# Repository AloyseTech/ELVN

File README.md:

# ELVN

ELVN is ARM Cortex M0+ development board based on the SAMD11 microcontroller. This repository contains hardware and firmware related to this board, including development tool (host software etc).

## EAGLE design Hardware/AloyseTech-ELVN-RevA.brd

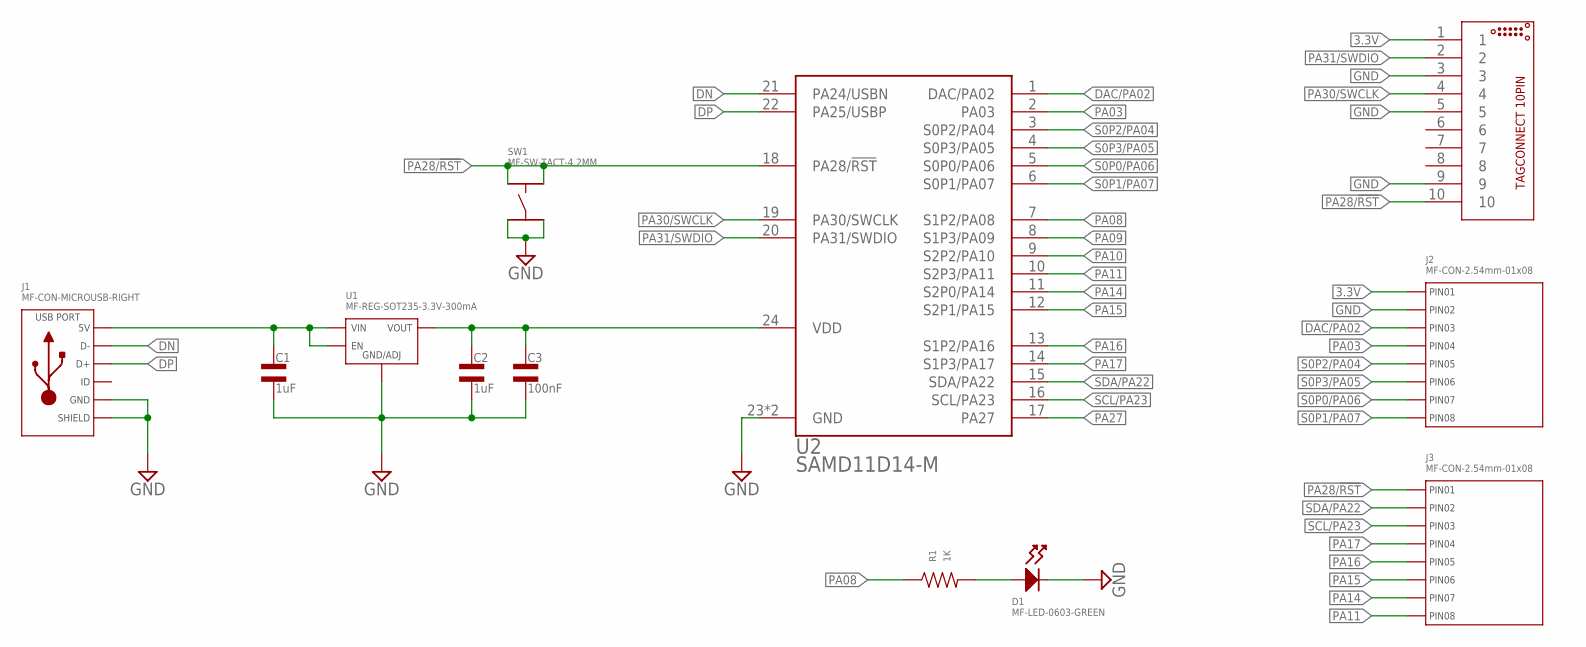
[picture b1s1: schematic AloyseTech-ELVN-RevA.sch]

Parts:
C1, C2: 1uF; 0805
C3: 100nF; 0402
D1: MF-LED-0603-GREEN; LED0603
J1: MF-CON-MICROUSB-RIGHT; MICROUSB-RIGHT
J2, J3: MF-CON-2.54mm-01x08; PTH_2.54MM_01X08
J4: TC2050-COMBO-NC; TC2050-10PIN1.27MM-COMBO-NC
R1: 1K; R0402
SW1: MF-SW-TACT-4.2MM; TACT4.2MM
U1: MF-REG-SOT235-3.3V-300mA; SOT-23-5
U2: SAMD11D14-M; QFN50P400X400X90-25T275

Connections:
3.3V: C2.1, C3.1, J2.P$1 (PIN1), J4.1, U1.P$5 (VOUT), U2.24 (VDD)
DAC/PA02: J2.P$3 (PIN3), U2.1 (DAC/PA02)
DN: J1.2 (D-), U2.21 (PA24/USBN)
DP: J1.3 (D+), U2.22 (PA25/USBP)
GND: C1.2, C2.2, C3.2, D1.CATHODE, J1.5 (GND), J1.S1 (SLD), J1.S2 (SLD), J1.S3 (SLD), J1.S4 (SLD), J1.S5 (SLD), J1.S6 (SLD), J2.P$2 (PIN2), J4.3, J4.5, J4.9, SW1.P$3, SW1.P$4, U1.P$2 (GND/ADJ), U2.23 (GND), U2.25 (GND)
unnamed: D1.ANODE, R1.P$2
PA03: J2.P$4 (PIN4), U2.2 (PA03)
PA08: R1.P$1, U2.7 (S1P2/PA08)
PA09: U2.8 (S1P3/PA09)
PA10: U2.9 (S2P2/PA10)
PA11: J3.P$8 (PIN8), U2.10 (S2P3/PA11)
PA14: J3.P$7 (PIN7), U2.11 (S2P0/PA14)
PA15: J3.P$6 (PIN6), U2.12 (S2P1/PA15)
PA16: J3.P$5 (PIN5), U2.13 (S1P2/PA16)
PA17: J3.P$4 (PIN4), U2.14 (S1P3/PA17)
PA27: U2.17 (PA27)
PA28/!RST!: J3.P$1 (PIN1), J4.10, SW1.P$1, SW1.P$2, U2.18 (PA28/!RST!)
PA30/SWCLK: J4.4, U2.19 (PA30/SWCLK)
PA31/SWDIO: J4.2, U2.20 (PA31/SWDIO)
S0P0/PA06: J2.P$7 (PIN7), U2.5 (S0P0/PA06)
S0P1/PA07: J2.P$8 (PIN8), U2.6 (S0P1/PA07)
S0P2/PA04: J2.P$5 (PIN5), U2.3 (S0P2/PA04)
S0P3/PA05: J2.P$6 (PIN6), U2.4 (S0P3/PA05)
SCL/PA23: J3.P$3 (PIN3), U2.16 (SCL/PA23)
SDA/PA22: J3.P$2 (PIN2), U2.15 (SDA/PA22)
VBUS: C1.1, J1.1 (5V), U1.P$1 (VIN), U1.P$3 (EN)

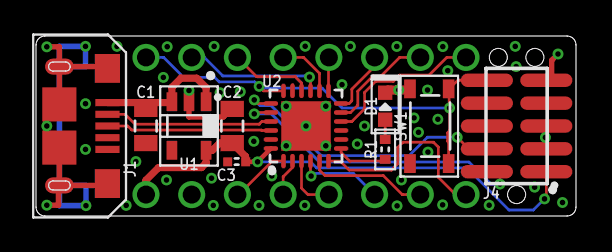
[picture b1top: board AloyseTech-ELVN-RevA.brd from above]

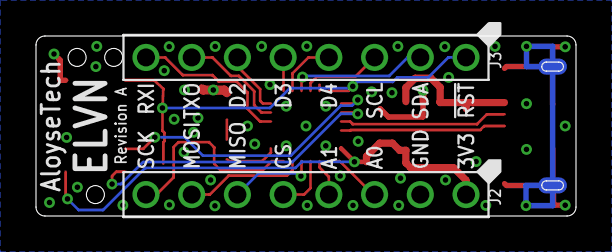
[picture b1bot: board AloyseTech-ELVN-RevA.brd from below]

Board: 2 copper layers, 30.0 x 10.0 mm, 12 parts (2 on the bottom side), 23 nets.

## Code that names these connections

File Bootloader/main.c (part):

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#define UART_SERCOM_APBCMASK     PM_APBCMASK_SERCOM0
#define UART_SERCOM_TXPO         2
#define UART_SERCOM_RXPO         0
#define UART_TX_PIN              4 // PA04
#define UART_RX_PIN              6 // PA06
#define UART_SERCOM_GCLK	     8000000ul
#define UART_BAUDRATE		     115200ul
#define UART_BAUD_VAL	         (65536.0*(1.0-((float)(16.0*(float)UART_BAUDRATE)/(float)UART_SERCOM_GCLK)))
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	#endif
	
	#ifdef BL_ENTRY_ON_LOW_PIN
	/* configure PA15 (bootloader entry pin used by SAM-BA) as input pull-up */
	//PORT->Group[0].PINCFG[BL_ENTRY_ON_LOW_PIN].reg = PORT_PINCFG_PULLEN | PORT_PINCFG_INEN;
	//PORT->Group[0].OUTSET.reg = (1UL << BL_ENTRY_ON_LOW_PIN);
	#if BL_ENTRY_ON_LOW_PIN <= 15
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	//PORT->Group[0].PINCFG[25].reg |= PORT_PINCFG_PMUXEN;
	//PORT->Group[0].PMUX[24>>1].reg = PORT_PMUX_PMUXO(PORT_PMUX_PMUXE_G_Val) | PORT_PMUX_PMUXE(PORT_PMUX_PMUXE_G_Val);

	/* Configure PA24 and PA25 for USB simultaneously */
	//TODO: should PULLUP be enabled by default
	PORT->Group[0].WRCONFIG.reg = PORT_WRCONFIG_HWSEL | PORT_WRCONFIG_WRPINCFG | PORT_WRCONFIG_WRPMUX
	| PORT_WRCONFIG_PMUX(PORT_PMUX_PMUXE_G_Val) | PORT_WRCONFIG_PMUXEN | PORT_WRCONFIG_PINMASK((1 << (25 - 16)) | (1 << (24 - 16)));
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
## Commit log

2019-04-18 make the bootloader fit in 1024 bytes of flash with entry on double rst tap, ram magic number detection and on bad crc
2019-04-18 use WRCONFIG for pin configuration (pin low for bootloader entry)
2019-04-18 ignore binary file
2019-04-18 ignore build dir
2019-04-19 fix WRCONFIG usage for 16bit pinmask
2019-04-19 Remove Blink project
2019-04-20 remove unecessaary linker and system file
2019-04-20 update as7 cproject
2019-04-20 fix linker to put stack in flash, fix PID to meet pid.codes development requirements, add led blink
2019-04-20 ignore debug build
2019-04-20 add debug config
2019-04-21 add dfu file converter from P. Lawrence, add dfu test firmwares
2019-04-21 Start adding UART feature
2019-04-21 rename bootloader project
2019-04-21 fix paths
2019-04-21 reorganize directory
2019-04-22 New project structure
2019-04-22 add hardware file
2019-04-22 add formware solution
2019-05-16 Create bootloader for SAMD11 variant

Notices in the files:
Bootloader/main.c:
Copyright (c) 2019, Theo Meyer <meyertheopro@gmail.com>
Copyright (c) 2018, Peter Lawrence
Copyright (c) 2016, Alex Taradov <alex@taradov.com>
All rights reserved.
parts and their libraries:
TagConnect_stg: ©2009 ROFA.cz - modified and updated by Robert Darlington ‹rdarlington@gmail.com›
